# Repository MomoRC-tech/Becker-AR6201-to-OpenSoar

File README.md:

# ✈️ Wi-Fi Bridge: Glider Avionics to OpenSoar

**FLARM · Zander ZS1 glider computer · Becker AR6201 radio → OpenSoar on Android**

A small ESP32 box in the glider that collects data from the cockpit instruments and sends it over Wi-Fi to OpenSoar on a phone or tablet. No cables run to the Android device.

- 📡 **Traffic:** FLARM collision-warning and position data appear in OpenSoar.
- 📈 **Flight data:** the Zander ZS1 sends flight and navigation data.
- 📻 **Radio:** pick an airfield in OpenSoar and its frequency goes into the Becker radio's standby slot.

> [!NOTE]
> **Status:** planning and bench design — nothing is built yet.
> **Current focus:** 🔧 hardware selection and wiring. Software work waits until the hardware design is finished.

📑 **On this page:** <kbd>[1 · 🎯 What it does](#what-it-does)</kbd> <kbd>[2 · 🚦 Project status](#status)</kbd> <kbd>[3 · 🗺️ Documentation map](#documentation)</kbd> <kbd>[4 · ⚠️ Safety](#safety)</kbd>

---

## 1. 🎯 What it does

| Device | What the bridge does |
| --- | --- |
| 📈 Glider computer: Zander ZS1 | Sends flight and navigation data to OpenSoar |
| 📡 Collision warning: Classic FLARM | Sends traffic and navigation data to OpenSoar |
| 📻 Radio: Becker AR6201 | Puts the selected airfield frequency into standby; reports radio status where supported |

The bridge never changes the active frequency, and the radio's own controls keep working. Not planned: active tuning, frequency swap, volume and squelch.

---

## 2. 🚦 Project status

| Stage | Status |
| --- | --- |
| 🔬 Research and documentation | ✅ Done |
| 🔧 Hardware selection and wiring | 🟡 **In progress** — wiring design and bench checks open |
| 🛩️ Existing installation details | 🟡 Waiting for equipment information |
| 💻 Firmware and driver changes | ⏸️ On hold until the hardware is finished |
| ✈️ Aircraft integration | ⬜ Later |

**Next step:** continue the wiring design in [WP3 Hardware](docs/project/roadmap.md#work-packages).

---

## 3. 🗺️ Documentation map

| | Section | Page | What you find there |
| :-: | --- | --- | --- |
| 🔧 | **Hardware** | [🔌 Signal wiring](docs/hardware/wiring.md) | Pin-by-pin signal wiring and bench bring-up |
| | | [⚡ Power and grounding](docs/hardware/power.md) | Supply, ground loops and currents |
| | | [🧱 Modules and parts](docs/hardware/modules.md) | Module details, parts list |
| | | [📦 Housing](docs/hardware/housing.md) | Mechanical design |
| | | [📐 CAD downloads and credits](cad/reference/README.md) | Reference models, original sources and reuse terms |
| 🧩 | **Design** | [🏗️ Architecture](docs/design/architecture.md) | How the bridge is built and why |
| | | [🎯 Requirements](docs/design/requirements.md) | Requirements, assumptions, risks |
| 📋 | **Project** | [🗺️ Roadmap](docs/project/roadmap.md) | Work plan |
| | | [💶 Hardware cost](docs/project/cost.md) | Cost breakdown for one bridge |
| | | [❓ Open items](docs/project/open-items.md) | Everything still missing |
| | | [🛩️ Existing installation](docs/project/existing-installation.md) | The bridge already in the aircraft |
| 🔬 | **Research** | [📚 Sources](docs/research/sources.md) | Evidence |
| | | [📻 Becker driver](docs/research/becker-driver.md) | Driver analysis |
| | | [📶 Bridge firmware](docs/research/bridge-firmware.md) | Firmware analysis |
| | | [🗂️ Reviews](docs/research/reviews) | Dated review records |

Working on the repository? Read the [work instructions](AGENTS.md) first.

---

## 4. ⚠️ Safety

> [!WARNING]
> Nothing here is verified on real hardware. Do the [bench checks](docs/project/open-items.md#bench-hardware) before connecting any aircraft equipment. The existing installation stays untouched as a backup.

---

<kbd>[⬆️ Back to top](#top)</kbd>

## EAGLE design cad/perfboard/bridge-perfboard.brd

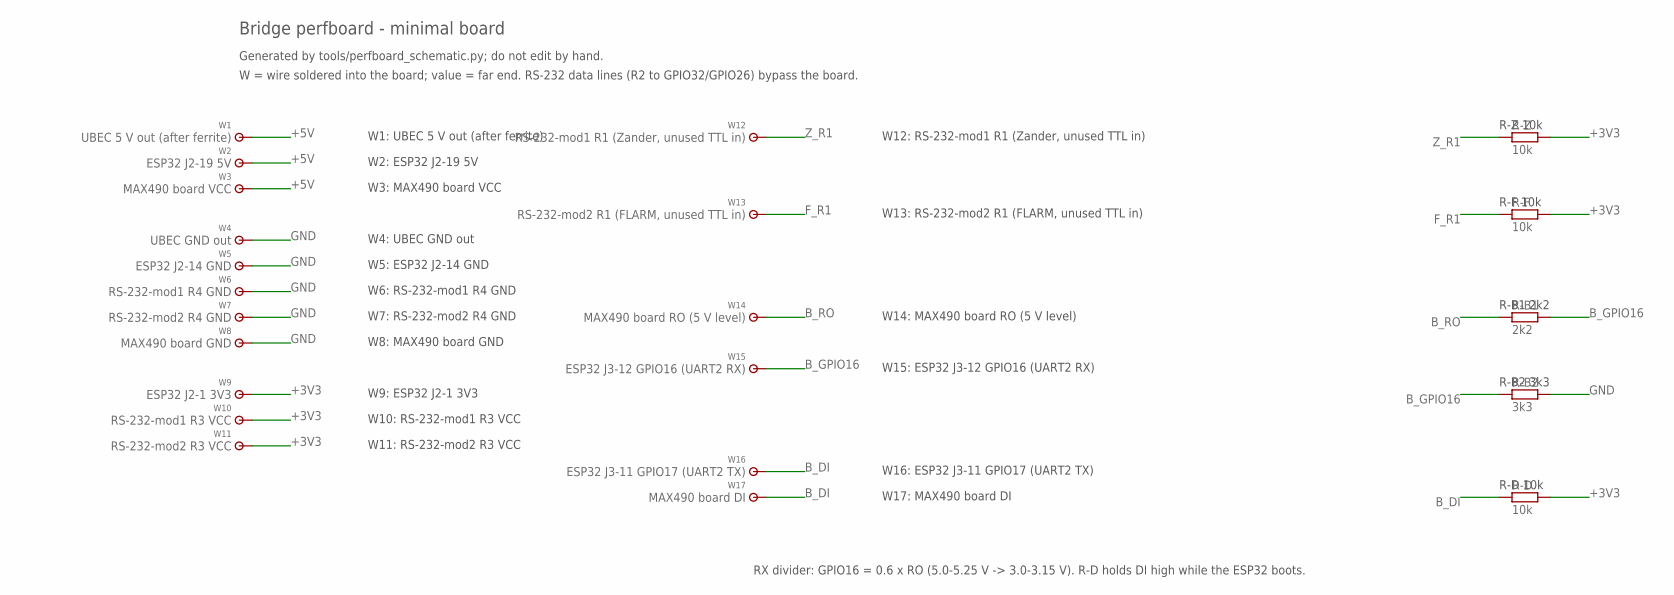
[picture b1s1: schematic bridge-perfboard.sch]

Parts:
R-B1: 2k2; R0204/7
R-B2: 3k3; R0204/7
R-D: 10k; R0204/7
R-F: 10k; R0204/7
R-Z: 10k; R0204/7
W1: UBEC 5 V out (after ferrite); WIREPAD
W2: ESP32 J2-19 5V; WIREPAD
W3: MAX490 board VCC; WIREPAD
W4: UBEC GND out; WIREPAD
W5: ESP32 J2-14 GND; WIREPAD
W6: RS-232-mod1 R4 GND; WIREPAD
W7: RS-232-mod2 R4 GND; WIREPAD
W8: MAX490 board GND; WIREPAD
W9: ESP32 J2-1 3V3; WIREPAD
W10: RS-232-mod1 R3 VCC; WIREPAD
W11: RS-232-mod2 R3 VCC; WIREPAD
W12: RS-232-mod1 R1 (Zander, unused TTL in); WIREPAD
W13: RS-232-mod2 R1 (FLARM, unused TTL in); WIREPAD
W14: MAX490 board RO (5 V level); WIREPAD
W15: ESP32 J3-12 GPIO16 (UART2 RX); WIREPAD
W16: ESP32 J3-11 GPIO17 (UART2 TX); WIREPAD
W17: MAX490 board DI; WIREPAD

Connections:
+3V3: R-D.2, R-F.2, R-Z.2, W9.1, W10.1, W11.1
+5V: W1.1, W2.1, W3.1
B_DI: R-D.1, W16.1, W17.1
B_GPIO16: R-B1.2, R-B2.1, W15.1
B_RO: R-B1.1, W14.1
F_R1: R-F.1, W13.1
GND: R-B2.2, W4.1, W5.1, W6.1, W7.1, W8.1
Z_R1: R-Z.1, W12.1

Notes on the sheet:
Bridge perfboard - minimal board
Generated by tools/perfboard_schematic.py; do not edit by hand.
W = wire soldered into the board; value = far end. RS-232 data lines (R2 to GPIO32/GPIO26) bypass the board.
RX divider: GPIO16 = 0.6 x RO (5.0-5.25 V -> 3.0-3.15 V). R-D holds DI high while the ESP32 boots.
W1: UBEC 5 V out (after ferrite)
W2: ESP32 J2-19 5V
W3: MAX490 board VCC
W4: UBEC GND out
W5: ESP32 J2-14 GND
W6: RS-232-mod1 R4 GND
W7: RS-232-mod2 R4 GND
W8: MAX490 board GND
W9: ESP32 J2-1 3V3
W10: RS-232-mod1 R3 VCC
W11: RS-232-mod2 R3 VCC
W12: RS-232-mod1 R1 (Zander, unused TTL in)
W13: RS-232-mod2 R1 (FLARM, unused TTL in)
W14: MAX490 board RO (5 V level)
W15: ESP32 J3-12 GPIO16 (UART2 RX)
W16: ESP32 J3-11 GPIO17 (UART2 TX)
W17: MAX490 board DI
R-Z 10k
R-F 10k
R-B1 2k2
R-B2 3k3
R-D 10k

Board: 1 copper layer, 22 parts (0 on the bottom side), 8 nets, no tracks yet.

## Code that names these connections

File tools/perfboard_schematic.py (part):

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    ("W12", "RS-232-mod1 R1 (Zander, unused TTL in)", "Z_R1", 40, 40),
    ("W13", "RS-232-mod2 R1 (FLARM, unused TTL in)", "F_R1", 40, 34),
    ("W14", "MAX490 board RO (5 V level)", "B_RO", 40, 26),
    ("W15", "ESP32 J3-12 GPIO16 (UART2 RX)", "B_GPIO16", 40, 22),
    ("W16", "ESP32 J3-11 GPIO17 (UART2 TX)", "B_DI", 40, 14),
    ("W17", "MAX490 board DI", "B_DI", 40, 12),
]

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RESISTORS = [
    ("R-Z", "10k", "Z_R1", "+3V3", 100, 40),
    ("R-F", "10k", "F_R1", "+3V3", 100, 34),
    ("R-B1", "2k2", "B_RO", "B_GPIO16", 100, 26),
    ("R-B2", "3k3", "B_GPIO16", "GND", 100, 20),
    ("R-D", "10k", "B_DI", "+3V3", 100, 12),
]

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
